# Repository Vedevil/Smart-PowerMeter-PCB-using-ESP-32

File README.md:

# Smart-PowerMeter-PCB-using-ESP-32
ESP32-based Smart Power Monitoring PCB with PZEM-004T, ACS712, and SCT013 sensors

⚡ Smart Power Monitor – PCB Design

The Smart Power Monitor PCB is an open-source hardware project built around the ESP32-WROOM-32 microcontroller, designed to measure and monitor voltage, current, power, and energy consumption in real time.

This PCB integrates support for three widely used energy measurement modules:

PZEM-004T – For accurate voltage, power, and energy measurement.

ACS712 – A Hall-effect current sensor for low-current measurements.

SCT013 – A non-invasive current clamp for higher AC load monitoring.

The design is tailored for IoT applications, where energy usage data can be logged, analyzed, and transmitted wirelessly. With the ESP32 at its core, this PCB is capable of connecting to MQTT brokers, cloud dashboards, or local monitoring systems, enabling use in smart homes, research labs, and industrial automation setups.

✨ Key Features

ESP32-WROOM-32 Controller – WiFi + Bluetooth connectivity out of the box.

Multi-Sensor Support – Compatible with PZEM-004T, ACS712, and SCT013.

Compact PCB Form Factor – Optimized 2-layer PCB for low-cost fabrication.

Open Source – All schematics, PCB files, and Gerbers are free to use.

IoT Ready – Designed for integration with MQTT dashboards, Home Assistant, or custom mobile apps.

Educational Value – Perfect for learning PCB design, IoT systems, and power electronics.

📐 Hardware Overview

Power Supply: 5V input via barrel jack or header.

Connectivity: UART/I²C headers for sensor interfacing.

Measurement Range:

Voltage: 80–260V AC (via PZEM-004T)

Current: 0–20A (via ACS712)

Current: up to 100A (via SCT013 clamp)

PCB Layers: 2 (optimized for easy manufacturing).

Software Support: Arduino IDE / PlatformIO with ESP32 libraries.

🛠️ Applications

Smart Home Energy Monitoring (track appliances, reduce consumption).

Industrial Load Monitoring (real-time analysis of machines and equipment).

IoT Dashboards (publish data to the cloud using MQTT/HTTP).

Academic & Research Projects (power electronics, embedded systems).

Low-cost alternative to commercial energy meters.

📦 Repository Contents

/hardware/ – KiCad schematic, PCB layout, Gerber files, BOM.

/docs/ – PCB renders, diagrams, and usage notes.

LICENSE – MIT License for free usage and modifications.

README.md – Documentation and project overview.

🔧 How to Get Started

Clone the repository:

git clone https://github.com/<your-username>/SmartPowerMonitor-PCB.git

Open the .sch and .kicad_pcb files in KiCad (v6+ recommended).

Export Gerbers using KiCad’s plot function.

Upload Gerbers (SmartPowerMonitor-Gerbers.zip) to PCB manufacturers (JLCPCB, PCBWay, etc.).

Order components from the BOM and assemble.

Flash ESP32 with your firmware to start monitoring energy.

📊 Example Workflow

Connect AC load to sensors (e.g., lamp, motor).

ESP32 reads measurements from PZEM-004T, ACS712, or SCT013.

Data is displayed via Serial Monitor or sent over WiFi.

MQTT broker or IoT dashboard logs the data.

User tracks real-time and historical energy consumption.

📜 License

This project is licensed under the MIT License – you are free to use, modify, and distribute, provided proper credit is given.
Schematic 

Layout

3D View

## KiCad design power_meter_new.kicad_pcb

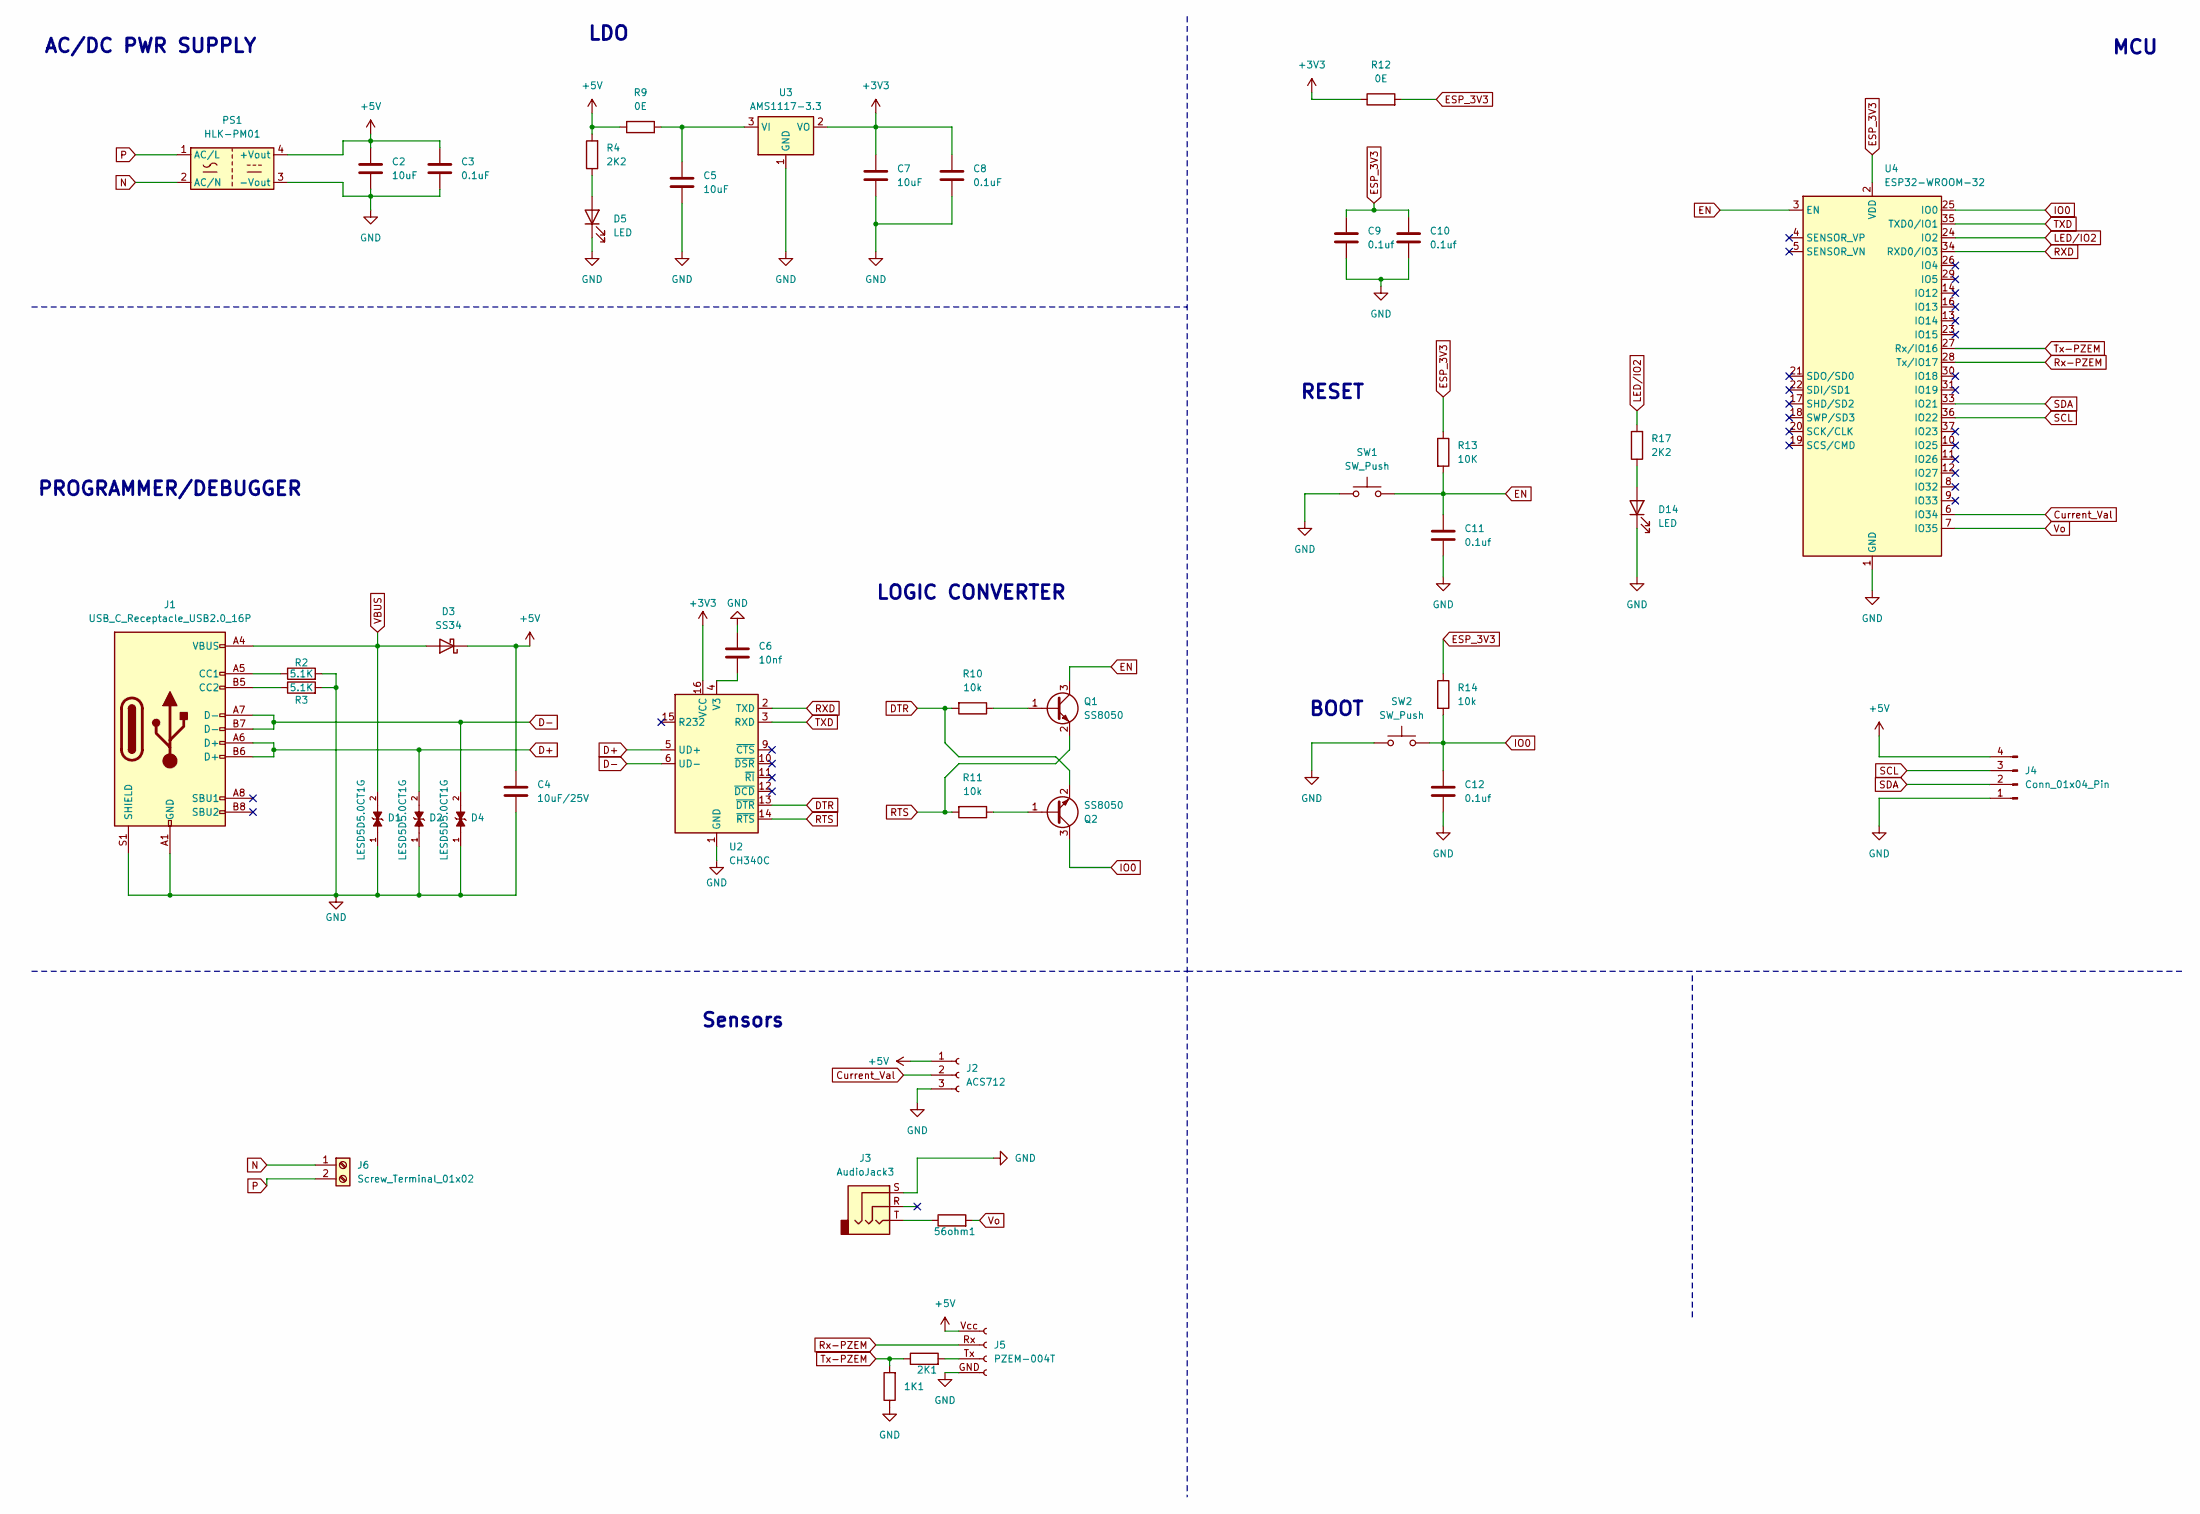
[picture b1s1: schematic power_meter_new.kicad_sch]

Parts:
1K1: 1K; R_0805_2012Metric
2K1, 56ohm1: 56; R_0805_2012Metric
C2, C5, C7: 10uF; C_1206_3216Metric
C3, C8: 0.1uF; C_0603_1608Metric
C4: 10uF/25V; C_0603_1608Metric
C6: 10nf; C_1206_3216Metric
C9, C10, C11, C12: 0.1uf; C_0603_1608Metric
D1, D2, D4: LESD5D5.0CT1G; TVS_LESD5D5.0CT1G; PARTREV O
D3: SS34; D_SMA
D5, D14: LED; LED_0603_1608Metric
J1: USB_C_Receptacle_USB2.0_16P; USB_C_Receptacle_HCTL_HC-TYPE-C-16P-01A
J2: ACS712; JST_PH_S3B-PH-K_1x03_P2.00mm_Horizontal
J3: AudioJack3; Jack_3.5mm_CUI_SJ-3523-SMT_Horizontal
J4: Conn_01x04_Pin; PinHeader_1x04_P2.54mm_Vertical
J5: PZEM-004T; JST_PH_B4B-PH-K_1x04_P2.00mm_Vertical
J6: Screw_Terminal_01x02; TerminalBlock_bornier-2_P5.08mm
PS1: HLK-PM01; Converter_ACDC_Hi-Link_HLK-PMxx
Q1, Q2: SS8050; SOT-23
R2, R3: 5.1K; R_0603_1608Metric
R4, R17: 2K2; R_0603_1608Metric
R9, R12: 0E; R_0603_1608Metric
R10, R11, R14: 10k; R_0603_1608Metric
R13: 10K; R_0603_1608Metric
SW1, SW2: SW_Push; SW_Push_SPST_NO_Alps_SKRK
U2: CH340C; SOIC-16_3.9x9.9mm_P1.27mm
U3: AMS1117-3.3; SOT-223-3_TabPin2
U4: ESP32-WROOM-32

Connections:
+3V3: C7.1, C8.1, R12.1, U2.16 (VCC), U3.2 (VO)
+5V: C2.1, C3.1, C4.1, D3.1 (K), J2.1, J4.4, J5.Vcc (Pin_1), PS1.4 (+Vout), R4.2, R9.1
Current_Val: J2.2, U4.6 (IO34)
D+: D2.2, J1.A6 (D+), J1.B6 (D+), U2.5 (UD+)
D-: D4.2, J1.A7 (D-), J1.B7 (D-), U2.6 (UD-)
DTR: Q2.2 (E), R10.2, U2.13 (~DTR)
EN: C11.1, Q1.3 (C), R13.2, SW1.2, U4.3 (EN)
ESP_3V3: C9.1, C10.1, R12.2, R13.1, R14.1, U4.2 (VDD)
GND: 1K1.1, C2.2, C3.2, C4.2, C5.2, C6.1, C7.2, C8.2, C9.2, C10.2, C11.2, C12.2, D1.1, D2.1, D4.1, D5.1 (K), D14.1 (K), J1.A1 (GND), J1.A12 (GND), J1.B1 (GND), J1.B12 (GND), J1.S1 (SHIELD), J2.3, J3.S, J4.1, J5.GND (Pin_4), PS1.3 (-Vout), R2.2, R3.2, SW1.1, SW2.1, U2.1 (GND), U3.1 (GND), U4.1 (GND), U4.15 (GND), U4.38 (GND), U4.39 (GND)
IO0: C12.1, Q2.3 (C), R14.2, SW2.2, U4.25 (IO0)
LED/IO2: R17.2, U4.24 (IO2)
N: J6.1, PS1.2 (AC/N)
unnamed: 56ohm1.1, J3.T
unnamed: D5.2 (A), R4.1
unnamed: D14.2 (A), R17.1
unnamed: J1.A5 (CC1), R2.1
unnamed: J1.B5 (CC2), R3.1
unnamed: 2K1.2, J5.Tx (Pin_3)
unnamed: Q1.1 (B), R10.1
unnamed: Q2.1 (B), R11.1
unnamed: C6.2, U2.4 (V3)
unnamed: C5.1, R9.2, U3.3 (VI)
P: J6.2, PS1.1 (AC/L)
RTS: Q1.2 (E), R11.2, U2.14 (~RTS)
RXD: U2.2 (TXD), U4.34 (RXD0/IO3)
Rx-PZEM: J5.Rx (Pin_2), U4.28 (Tx/IO17)
SCL: J4.3, U4.36 (IO22)
SDA: J4.2, U4.33 (IO21)
TXD: U2.3 (RXD), U4.35 (TXD0/IO1)
Tx-PZEM: 1K1.2, 2K1.1, U4.27 (Rx/IO16)
VBUS: D1.2, D3.2 (A), J1.A4 (VBUS), J1.A9 (VBUS), J1.B4 (VBUS), J1.B9 (VBUS)
Vo: 56ohm1.2, U4.7 (IO35)

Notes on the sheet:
MCU
LDO
LOGIC CONVERTER
AC/DC PWR SUPPLY
RESET
Sensors
BOOT
PROGRAMMER/DEBUGGER

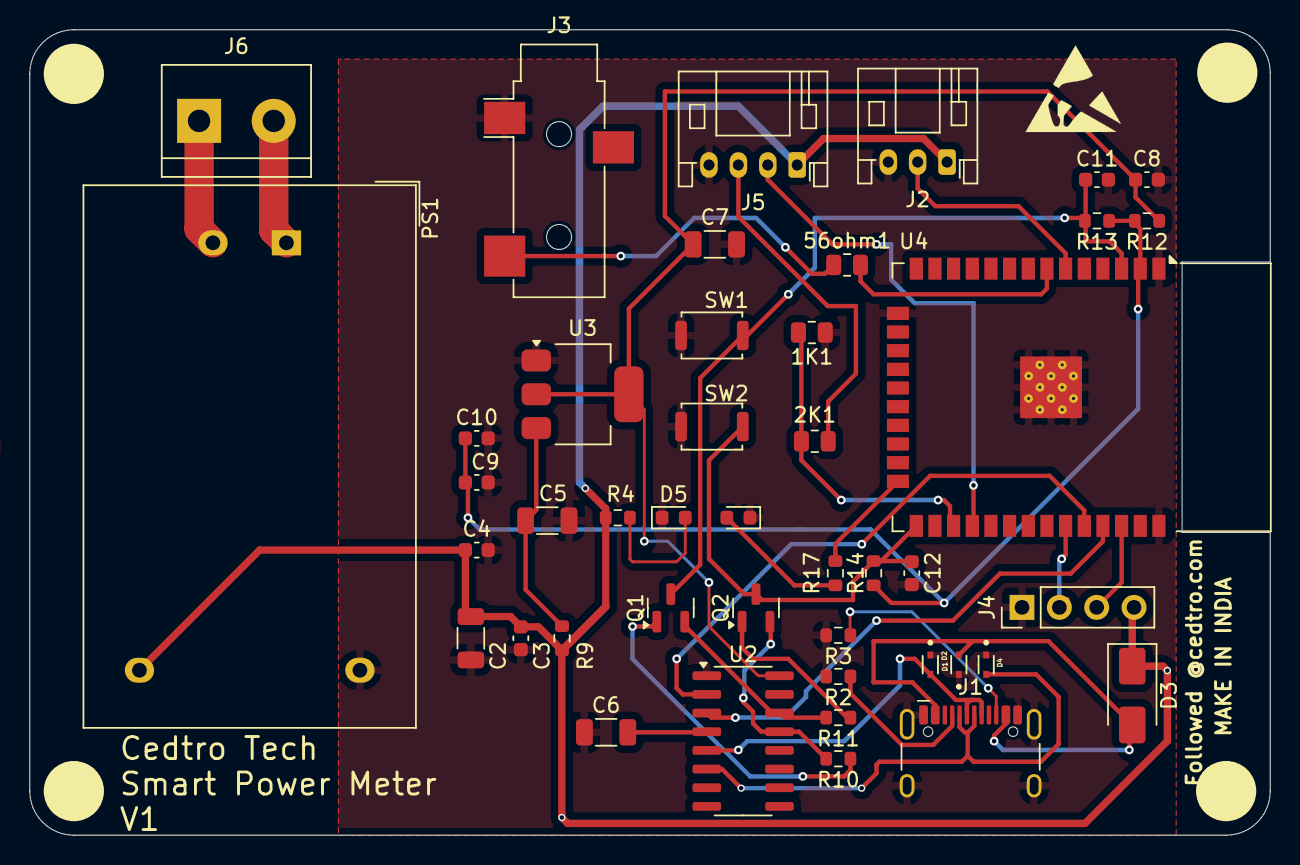
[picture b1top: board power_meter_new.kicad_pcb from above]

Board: 2 copper layers, 84.4 x 54.8 mm, 44 parts (0 on the bottom side), 32 nets.
